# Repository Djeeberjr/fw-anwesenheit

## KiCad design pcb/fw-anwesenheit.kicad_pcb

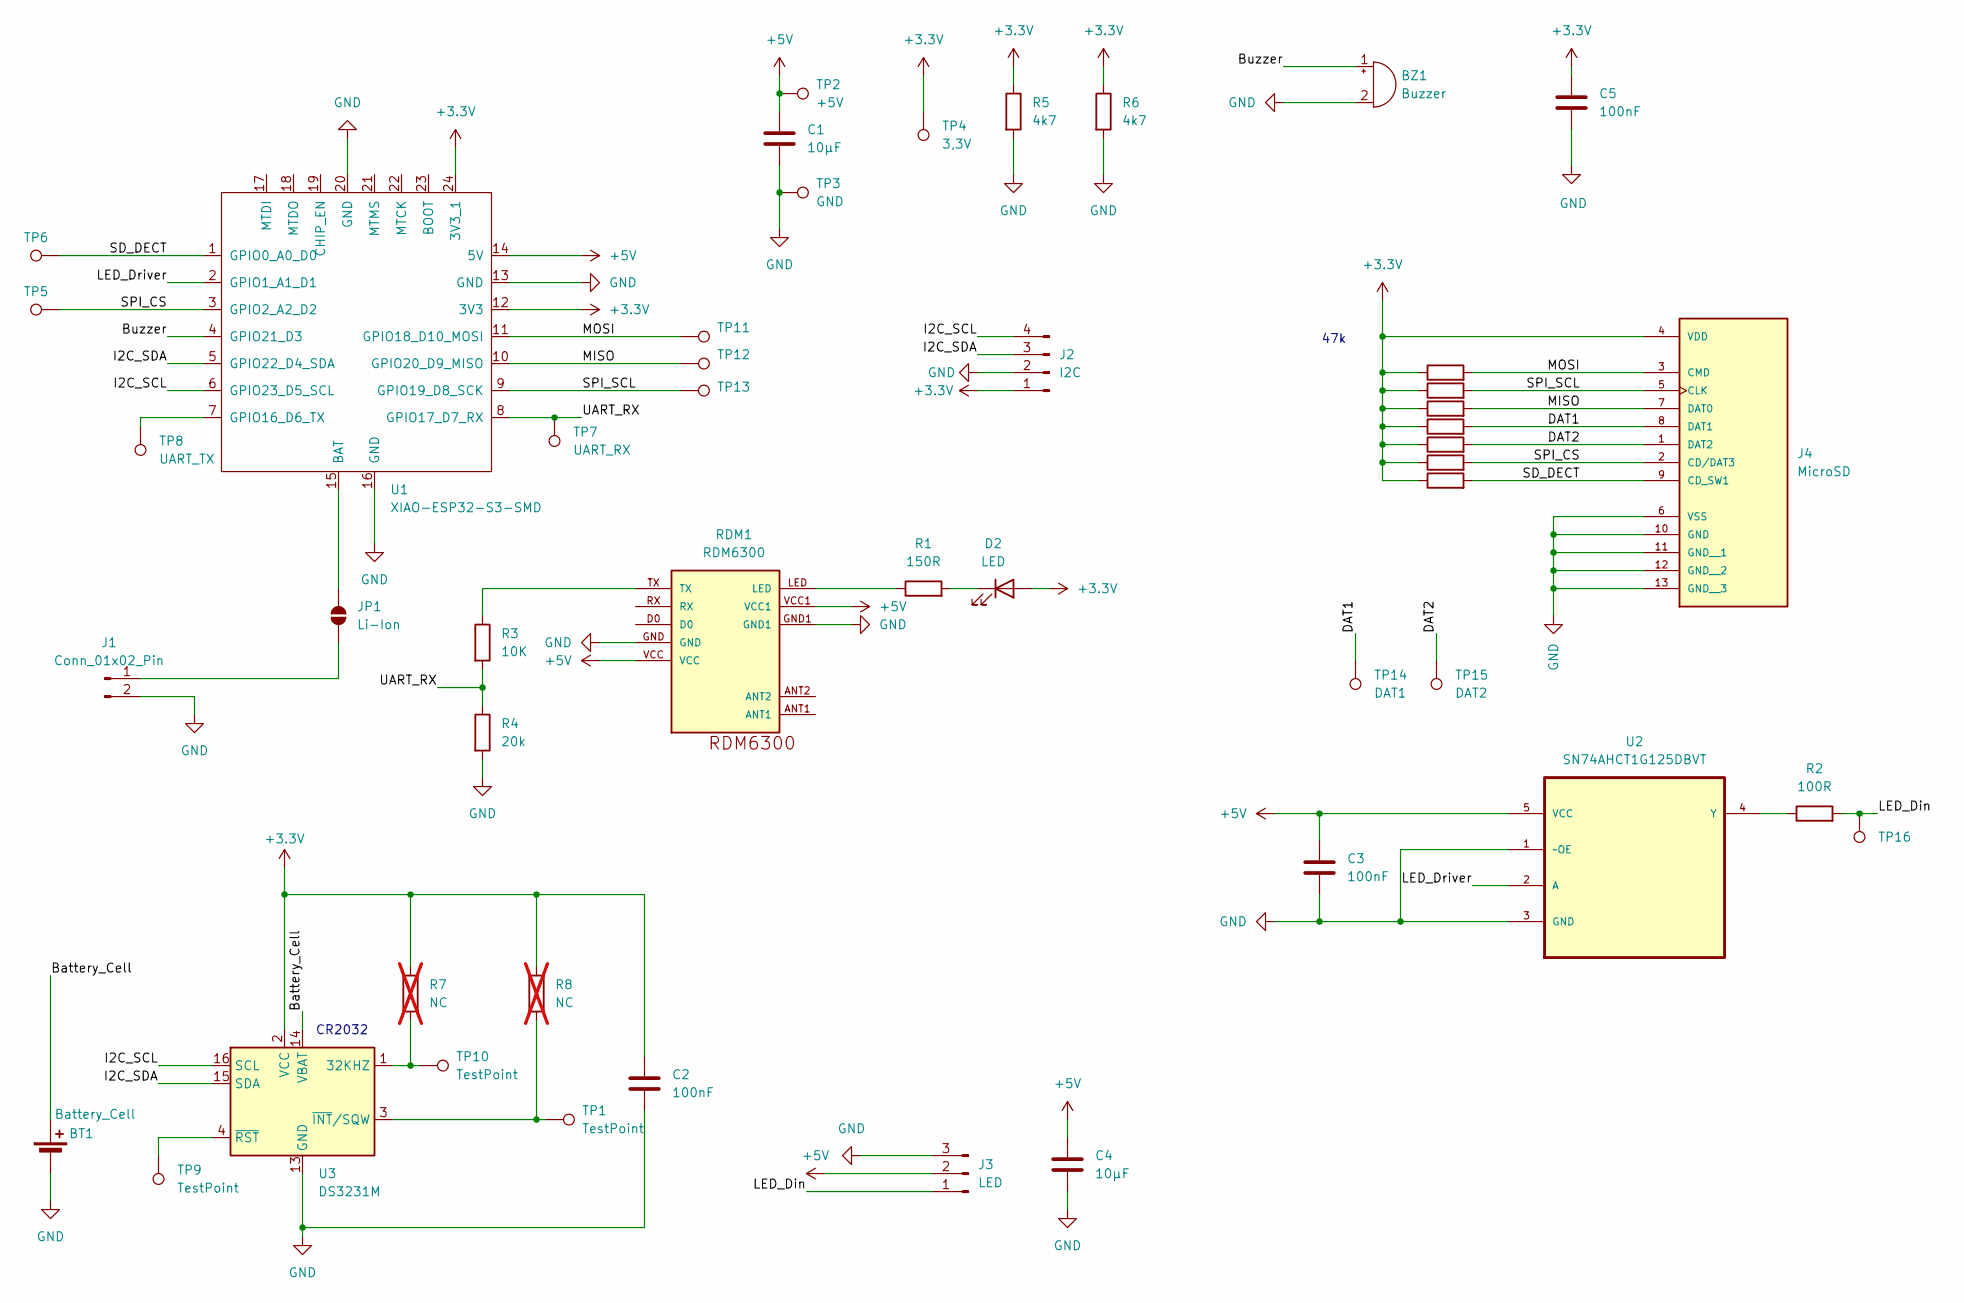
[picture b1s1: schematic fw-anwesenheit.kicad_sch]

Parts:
BT1: Battery_Cell; Battery_Panasonic_CR2032-HFN_Horizontal_CircularHoles
BZ1: Buzzer; PinSocket_1x02_P2.54mm_Vertical
C1, C4: 10µF; C_0603_1608Metric
C2, C3, C5: 100nF; C_0603_1608Metric
D2: LED; LED_0603_1608Metric
J1: Conn_01x02_Pin; PinHeader_1x02_P2.54mm_Vertical
J2: I2C; PinHeader_1x04_P2.54mm_Vertical
J3: LED; PinSocket_1x03_P2.00mm_Vertical
J4: MicroSD; WURTH_693071020811; PARTREV 001.003
JP1: Li-Ion; SolderJumper-2_P1.3mm_Open_TrianglePad1.0x1.5mm
R1: 150R; R_0603_1608Metric_Pad0.98x0.95mm_HandSolder
R2: 100R; R_0603_1608Metric_Pad0.98x0.95mm_HandSolder
R3: 10K; R_0603_1608Metric_Pad0.98x0.95mm_HandSolder
R4: 20k; R_0603_1608Metric_Pad0.98x0.95mm_HandSolder
R5, R6: 4k7; R_0603_1608Metric_Pad0.98x0.95mm_HandSolder
R7, R8: NC; R_0603_1608Metric_Pad0.98x0.95mm_HandSolder; not fitted
R9, R10, R11, R12, R13, R14, R15: 47k; R_0603_1608Metric_Pad0.98x0.95mm_HandSolder
RDM1: RDM6300
TP1, TP9, TP10: TestPoint; TestPoint_Pad_D1.5mm
TP2: +5V; TestPoint_Pad_D1.5mm
TP3: GND; TestPoint_Pad_D1.5mm
TP4: 3,3V; TestPoint_Pad_D1.5mm
TP5: CS; TestPoint_Pad_D1.5mm
TP6: SD_DECT; TestPoint_Pad_D1.5mm
TP7: UART_RX; TestPoint_Pad_D1.5mm
TP8: UART_TX; TestPoint_Pad_D1.5mm
TP11: MOSI; TestPoint_Pad_D1.5mm
TP12: MISO; TestPoint_Pad_D1.5mm
TP13: SPI SCL; TestPoint_Pad_D1.5mm
TP14: DAT1; TestPoint_Pad_D1.5mm
TP15: DAT2; TestPoint_Pad_D1.5mm
TP16: LED_Din; TestPoint_Pad_D1.5mm
U1: XIAO-ESP32-S3-SMD; XIAO-ESP32C6-SMD
U2: SN74AHCT1G125DBVT; SOT95P280X145-5N; MPN SN74AHCT1G125DBVT
U3: DS3231M; SOIC-16W_7.5x10.3mm_P1.27mm

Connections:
+3.3V: C2.2, C5.2, D2.2 (A), J2.1, J4.4 (VDD), R5.1, R6.1, R7.1, R8.1, R9.1, R10.1, R11.1, R12.1, R13.1, R14.1, R15.1, TP4.1, U1.12 (3V3), U1.24 (3V3_1), U3.2 (VCC)
+5V: C1.2, C3.2, C4.2, J3.2, RDM1.VCC, RDM1.VCC1, TP2.1, U1.14 (5V), U2.5 (VCC)
/Battery_Cell: BT1.1 (+), U3.14 (VBAT)
/Buzzer: BZ1.1 (+), U1.4 (GPIO21_D3)
/DAT1: J4.8 (DAT1), R10.2, TP14.1
/DAT2: J4.1 (DAT2), R15.2, TP15.1
/I2C_SCL: J2.4, U1.6 (GPIO23_D5_SCL), U3.16 (SCL)
/I2C_SDA: J2.3, U1.5 (GPIO22_D4_SDA), U3.15 (SDA)
/LED_Driver: U1.2 (GPIO1_A1_D1), U2.2 (A)
/MISO: J4.7 (DAT0), R12.2, TP12.1, U1.10 (GPIO20_D9_MISO)
/MOSI: J4.3 (CMD), R14.2, TP11.1, U1.11 (GPIO18_D10_MOSI)
/SD_DECT: J4.9 (CD_SW1), R11.2, TP6.1, U1.1 (GPIO0_A0_D0)
/SPI_SCL: J4.5 (CLK), R13.2, TP13.1, U1.9 (GPIO19_D8_SCK)
/UART_RX: R3.2, R4.1, TP7.1, U1.8 (GPIO17_D7_RX)
GND: BT1.2 (-), BZ1.2 (-), C1.1, C2.1, C3.1, C4.1, C5.1, J1.2, J2.2, J3.3, J4.6 (VSS), J4.10 (GND), J4.11 (GND__1), J4.12 (GND__2), J4.13 (GND__3), R4.2, R5.2, R6.2, RDM1.GND, RDM1.GND1, TP3.1, U1.13 (GND), U1.16 (GND), U1.20 (GND), U2.1 (~OE), U2.3 (GND), U3.5 (GND), U3.6 (GND), U3.7 (GND), U3.8 (GND), U3.9 (GND), U3.10 (GND), U3.11 (GND), U3.12 (GND), U3.13 (GND)
unnamed: D2.1 (K), R1.2
unnamed: J1.1, JP1.2 (B)
unnamed: JP1.1 (A), U1.15 (BAT)
unnamed: R1.1, RDM1.LED
unnamed: R3.1, RDM1.TX
unnamed: TP8.1, U1.7 (GPIO16_D6_TX)
unnamed: R2.1, U2.4 (Y)
unnamed: R7.2, TP10.1, U3.1 (32KHZ)
unnamed: R8.2, TP1.1, U3.3 (~INT/SQW)
unnamed: TP9.1, U3.4 (~RST)

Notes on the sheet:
CR2032
47k

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
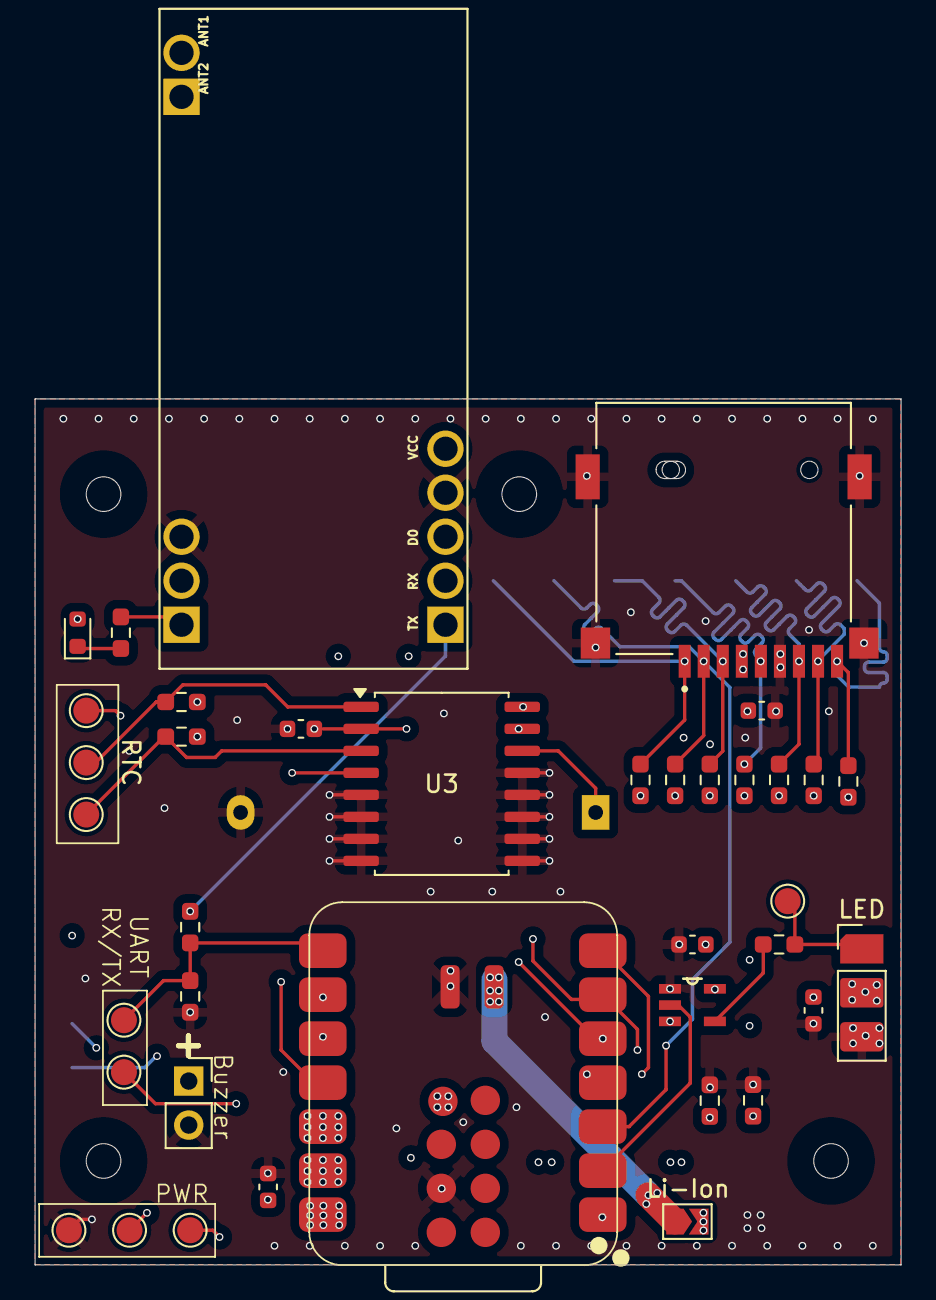
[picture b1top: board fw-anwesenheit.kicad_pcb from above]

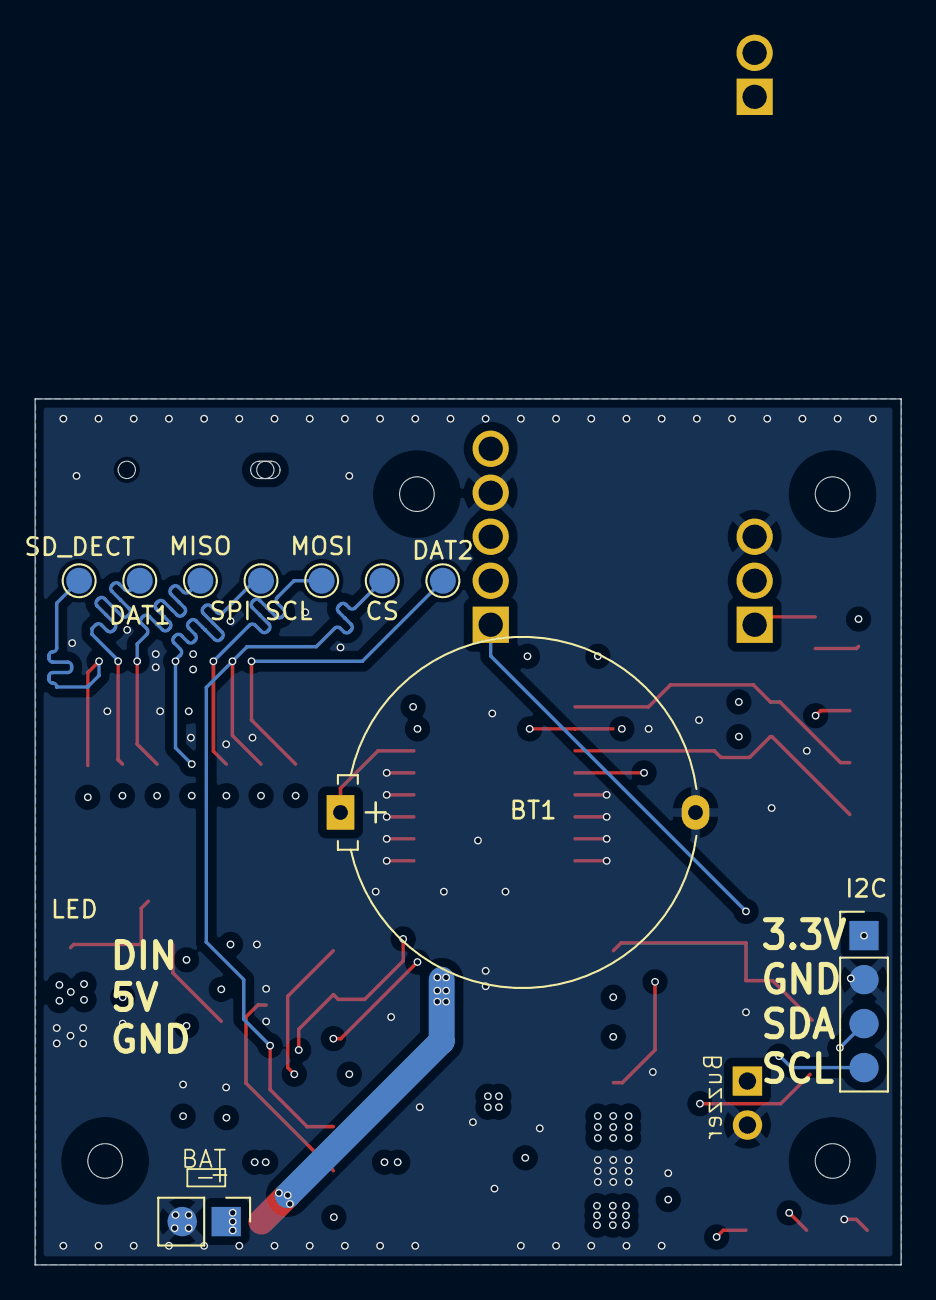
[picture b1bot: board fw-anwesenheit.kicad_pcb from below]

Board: 6 copper layers, 50.0 x 50.0 mm, 48 parts (10 on the bottom side), 27 nets.

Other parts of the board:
TP5#2: CS; TestPoint_Pad_D1.5mm

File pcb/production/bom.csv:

Designator,Footprint,Quantity,Value,LCSC Part #
BT1,Battery_Panasonic_CR2032-HFN_Horizontal_CircularHoles,1,Battery_Cell,
BZ1,PinSocket_1x02_P2.54mm_Vertical,1,Buzzer,
"C1, C4",0603,2,10µF,
"C2, C3, C5",0603,3,100nF,
D2,0603,1,LED,
J1,PinHeader_1x02_P2.54mm_Vertical,1,Conn_01x02_Pin,
J2,PinHeader_1x04_P2.54mm_Vertical,1,I2C,
J3,PinHeader_1x03_P2.54mm_Vertical,1,LED,
J4,WURTH_693071020811,1,MicroSD,
R1,0603,1,150R,
"R10, R11, R12, R13, R14, R15, R9",0603,7,47k,
R2,0603,1,100R,
R3,0603,1,10K,
R4,0603,1,20k,
"R5, R6",0603,2,4k7,
"R7, R8",0603,2,NC,
RDM1,RDM6300,1,RDM6300,
"TP1, TP10, TP9",TestPoint_Pad_D1.5mm,3,TestPoint,
TP11,TestPoint_Pad_D1.5mm,1,MOSI,
TP12,TestPoint_Pad_D1.5mm,1,MISO,
TP13,TestPoint_Pad_D1.5mm,1,SPI SCL,
TP14,TestPoint_Pad_D1.5mm,1,DAT1,
TP15,TestPoint_Pad_D1.5mm,1,DAT2,
TP2,TestPoint_Pad_D1.5mm,1,+5V,
TP3,TestPoint_Pad_D1.5mm,1,GND,
TP4,TestPoint_Pad_D1.5mm,1,"3,3V",
TP5_2,TestPoint_Pad_D1.5mm,1,Din,
TP5,TestPoint_Pad_D1.5mm,1,CS,
TP6,TestPoint_Pad_D1.5mm,1,SD_DECT,
TP7,TestPoint_Pad_D1.5mm,1,UART_RX,
TP8,TestPoint_Pad_D1.5mm,1,UART_TX,
U1,XIAO-ESP32C6-SMD,1,XIAO-ESP32-S3-SMD,
U2,SOT95P280X145-5N,1,SN74AHCT1G125DBVT,SN74AHCT1G125DBVT
U3,SOIC-16W_7.5x10.3mm_P1.27mm,1,DS3231M,

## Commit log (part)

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2025-04-12 implemented IDStore
2025-04-12 crated sequencediagram for HITAG reading
2025-04-16 use channels in pm3 function
2025-04-16 added buzzer
2025-04-16 Switched to tokio and added webserver
2025-04-16 updated some dependencies
2025-04-16 merge
2025-04-16 fixed git fuck up
2025-04-16 added web frontend files
2025-04-16 added arm target in .toml fixed some shit
2025-04-16 added export_csv to id_store
    Also some fixes and formatting
2025-04-16 workday ending
2025-04-16 CSV generation in the webserver
2025-04-22 download csv button now works
2025-04-22 added favicon
2025-04-23 add option to set pm3 binary
2025-04-23 added precompiled files, autorun service and changed tokyo buffer to one
2025-04-24 fixed missing executable bit in pre-compiled
2025-04-24 removed some debug lines
2025-04-25 added hotspot functions
    WIP
2025-04-26 added logger
    LOG_LEVEL env var is now supported
2025-04-26 added some documentation
2025-04-27 load store file on startup
2025-04-27 save store on new id
2025-04-27 minor improvements in pm3.rs
    - use trace instead of debug
    - use a loop instead of while true
    - ? operator on child.wait()
2025-04-27 moved store saving to main
2025-04-27 made logging less verbose
2025-04-27 use tokios command crate instead of the std one
    also removed pm3_mock as it is no longer needed
2025-04-27 added a simple pm3 mock script for testing
    use the PM3_BIN env var to use it
2025-04-27 removed unused pm3_mock import
2025-04-27 use the tokio fs in id store
    außerdem "readed_string" also bitte
2025-04-28 use HTTP_PORT env var for webserver port. Defaults to 80 now
2025-04-29 updated README with env vars
2025-05-05 added led ws 2812 and buzzer stuff
2025-05-05 fixed merge errors
2025-05-05 made buzzer async
2025-05-05 improved gpio buzzer
2025-05-05 fixed buzzer use in tokio thread
2025-05-05 fixed some buzzer timings
2025-05-05 improved Color enum
2025-05-05 added missing rgb dep
2025-05-08 Update README.md
    added instruction to enable PWM
2025-05-08 rewrited buzzer for 2,5kHz Buzzer and use PWM icreased SPI frequency to 3.8MHz
2025-05-12 improved buzzer
2025-05-12 fixed timings for LED
2025-05-12 added TODO and status LED
2025-05-12 improved hotspot functions
    with better error handeling & logging
2025-05-12 added HOTSPOT_IDS as an env var to enable hotspot with
2025-05-12 moved TallyID into it's own file
    Tally id now ignores tha case since it's basicly a hex value as a
    string. Reason for that is that if a user inputs an id.
2025-05-12 improved error handling in buzzer and led
2025-05-12 refactored led & buzzer feedback in main
2025-05-13 pm3: don't inherit stdin
2025-05-13 pm3_mock.sh output special ID on SIGUSR1
    for testing the hotspot
2025-05-13 implemented mocking of rpi hardware
    buzzer,led & hotspot got traits and a mock version of it. Based on the
    flag the real or mock version is used.
2025-05-13 updated README with hotspot config
2025-05-16 added id to name mapping module
2025-05-16 added IDMapping to IDStore
2025-05-16 added api route for id mappings
    also need rocket json feature
2025-05-16 added vite proxy for api in frontend
2025-05-16 simple display for id mappings in frontend
2025-05-16 switched to svelte 5
    front gets a bit to complex to do in vanilla
2025-05-17 implemented sorting in ID table
2025-05-18 implemented server side event stream for ids
    - changed channel to brodcast
    - added route /api/idevent for SSE stream
2025-05-18 display last scanned id on frontend
2025-05-20 added 3d print files
2025-05-20 prevent adding empty id mapping
2025-05-20 added Modal component
2025-05-20 added AddIDModal
2025-05-20 made data in IDTable reloadable
2025-05-20 inserted AddIDModal
2025-05-20 use name mapping when exporting to csv
2025-05-20 moved 3d_print directory
2025-05-21 removed missplaced target config
2025-05-22 moved systemd service file
2025-05-22 kill orphaned pm3 on startup
2025-05-22 pm3: id must be read twice
    to avoid false reads
2025-05-27 gracefull shutdown of PM3
2025-05-27 fixed WorkingDirectory in systemd service
2025-05-27 gracefull shutdown of SSE loop
2025-06-01 changed return type on Hotspot trait
2025-06-01 added activity_fairing for webserver
2025-06-01 disable hotspot when no activity on webserver
2025-06-01 refactored main function
    - moved logger into its own file
    - moved code from main into its own function
2025-06-01 refactored feedback & its depending stuff
    - buzzer is just modulate_tone
    - led is just turn on and off
    - handle feedback logic to feeback file
2025-06-02 refactored hardware components
    detach trait from mock and hardware implementation
2025-06-02 use anyhow for errors
2025-06-05 added error state flag
2025-06-05 fixed pm3 exit code
2025-06-05 moved systemd services
    also added env file for config
2025-06-05 added makefile for dep package
    closes #18
2025-06-05 improved Makefile
2025-06-09 create id mappings without prev ID
2025-06-17 added passive status led + startup sound
2025-06-18 code clean up
2025-06-25 improved readability
2025-06-26 moved related files into own module
2025-06-26 edit ids that are already mapped
2025-07-24 init v2
2025-07-24 added esp bootload
2025-07-26 improved project structure and hardware init
2025-07-26 first implementation of IDStore and IDmapping
2025-07-26 added embassy-sync crate
2025-07-26 implemented channel for TallyIDs
2025-07-26 added hardware files (rtc and fram)
2025-07-26 added i2c init
2025-07-27 addded lvl shifter init
2025-07-27 added some todos
2025-07-28 redesigned dir structure for rust 2018 style guide. made (untested) rtc funtion
2025-07-28 worted on rtc task, still not tested
2025-07-28 deleted todos for rtc
2025-07-28 added comment for Pinout
2025-07-30 added buzzer and rtc. rtc freeze the system, bevore interrupt can be initilized..
2025-07-30 added static assets on webserver
2025-08-01 buzzer without pwm, and feedback with embassy Sync. Error when more then 4 tasks spawn
2025-08-01 rtc is synchronized with compile time. start pub sub approach to share time
2025-08-04 reworked RTC without alarms and without own thread
2025-08-04 fixed embassy taks arena size
2025-08-11 chanched GPIO Pin configuration
2025-08-12 try to control LED with SmartLED and RMT
2025-08-12 test LED Array works..
2025-08-13 LED is working and implement in feedback
2025-08-13 still some errors with LED an levelshifter...
2025-08-15 Update hardware.rs
    changed pinlayout to add SD DECT top GPIO0
2025-08-15 circuit diagram is finish v1
2025-08-15 added serde for serializing in the webserver
2025-08-15 pcb v1 finish
2025-08-23 fixed RTC footprint and some labels
2025-09-01 updated pcb
2025-09-01 changed via size
2025-09-08 implemented SD card abstraction & used it in IDStore
2025-09-08 added todo
2025-09-08 implemented save function for SD Card
2025-09-09 there are some problems to implemet the IO Mux interrupt handler
2025-09-09 sd card detection works (own embassy task)
2025-09-21 changed some pcb descriptions and Resistor for LED
2025-09-21 fixed buzzer footprint
2025-09-21 deleted KiCAD backup files
2025-09-21 added some descriptions on pcb layout
2025-09-29 added pm3 write script & already used ids
2025-09-30 added kicad backups to gitignore
2025-10-01 fixed missing await
2025-10-01 return sdcard from hardware init
2025-10-01 updated enclousure top 3mf
2025-10-01 connect RFID reader with IDStore
2025-10-01 removed dummy data and pass read tally id
2025-10-01 new file will be created when sd card is empty
2025-10-04 changed Date to u8 array
2025-10-04 added get date method for rtc
2025-10-04 Update README with images and remove setup details
    Removed setup instructions and added images.
2025-10-07 added Deserialize to id mapping Name
2025-10-07 pined picoserve to current git version
2025-10-07 make network stack size a constant
2025-10-07 fixed webserver not working
    - shared store in main
    - multiple tasks for webserver
2025-10-07 changed NET_STACK_SIZE & WEB_TASK_SIZE
2025-10-07 12 chars of hex are 6 Bytes not 12
2025-10-07 moved TallyID str function to right module
2025-10-07 explicit type of tallyid channels
2025-10-07 implemented SSE
2025-10-07 fixed many warning by removing unused imports
    Removed a lot of imports — believe me, so many imports were totally
    unnecessary. Nobody’s seen imports like these. Cleaned up the code, made
    it faster, smarter, the best code. People are talking about it!
    Tremendous work by me. Some say i am the best at it. It may be true.
2025-10-08 changed TallyID to a struct instead of a type alias
2025-10-08 fixed RFID read id parser
2025-10-08 updated cargo lock
2025-10-09 changed Day implementation
2025-10-09 propper mapping of day to filename
2025-10-09 flatten IDMapping for serde
2025-10-09 added Deserialize to IDMapping
2025-10-09 implemented missing load & save mapping functions
2025-10-10 re-enabled mapping loading
2025-10-10 added mock server for frontedn dev
2025-10-10 fixed changed /api/mapping structure in frontend
2025-10-11 added Ord to Day
2025-10-11 fixed list_day for sd_card
2025-10-11 implemented Display for TallyID
2025-10-11 added TryFrom<[u8;12]> to TallyID
2025-10-11 fixed RFID reader outputting un-aligned IDs in buffer
2025-10-13 implemented load_day & list_day_in_timespan in IDStore
2025-10-13 added routes for listing days & getting days
    /api/days?from=...&to=...
    /api/day?day=...
2025-10-14 updated panic handler
2025-10-15 Revert "updated panic handler"
    This reverts commit c4d6ed45f1f57e92be21142b81a1fd2b52a5924f.
2025-10-15 renamed vars in main
2025-10-17 added new routes & more mock data to server mock
2025-10-17 added ExportModal
2025-10-17 added csv exporting logic
2025-10-20 added software resett after 10min when panic
2025-10-20 enabled download of exported csv
2025-10-20 simplified csv generator
2025-10-20 added downloadBlob function
2025-10-20 improved panic restart
2025-10-23 added umlaut user to mock data
2025-10-23 changed defaults in csv generation
2025-10-23 implemented year select for export csv
2025-10-23 added wifi password set at compiletime
2025-10-23 handle error in sse event route
2025-10-23 added missing persist mapping
2025-10-24 unwraps now give a warning
2025-10-25 feedback ack turns LED off after lighting green
2025-10-27 changed to new ESP libs WIP
2025-10-27 changed LED amount to 1
2025-10-27 moved LED and feedback to new lib
2025-10-27 implemented LED for new lib !esp-hhal-smartled is not released!
2025-10-27 improved hardware init
2025-10-27 deleted some imports
2025-10-27 improved wifi setup
2025-10-27 removed empty files
2025-10-27 improved networks stack & DHCP server
2025-10-27 pass current day to IDStore constructor
2025-10-27 removed unused code
2025-10-27 added red led flash in inti to see a failer on init routine
2025-10-27 chanched startup routine
2025-10-27 rtc will only setup with buildtime when it is larger then actual time in rtc
2025-10-27 bump vite version
2025-10-28 change sse event listner
2025-10-31 added counter for all mappings in ui
2025-11-03 enabled RTC
2025-11-03 changed TallyID deserializer to string insteand of str
2025-11-03 changed storage method of ID mappings
2025-11-03 improved error handeling for sdcard functions
2025-11-04 pessimistic id mapping loading on frontend
2025-11-04 chache idmap on client
2025-11-04 added gitattributes
2025-11-04 set log level in release build to info
